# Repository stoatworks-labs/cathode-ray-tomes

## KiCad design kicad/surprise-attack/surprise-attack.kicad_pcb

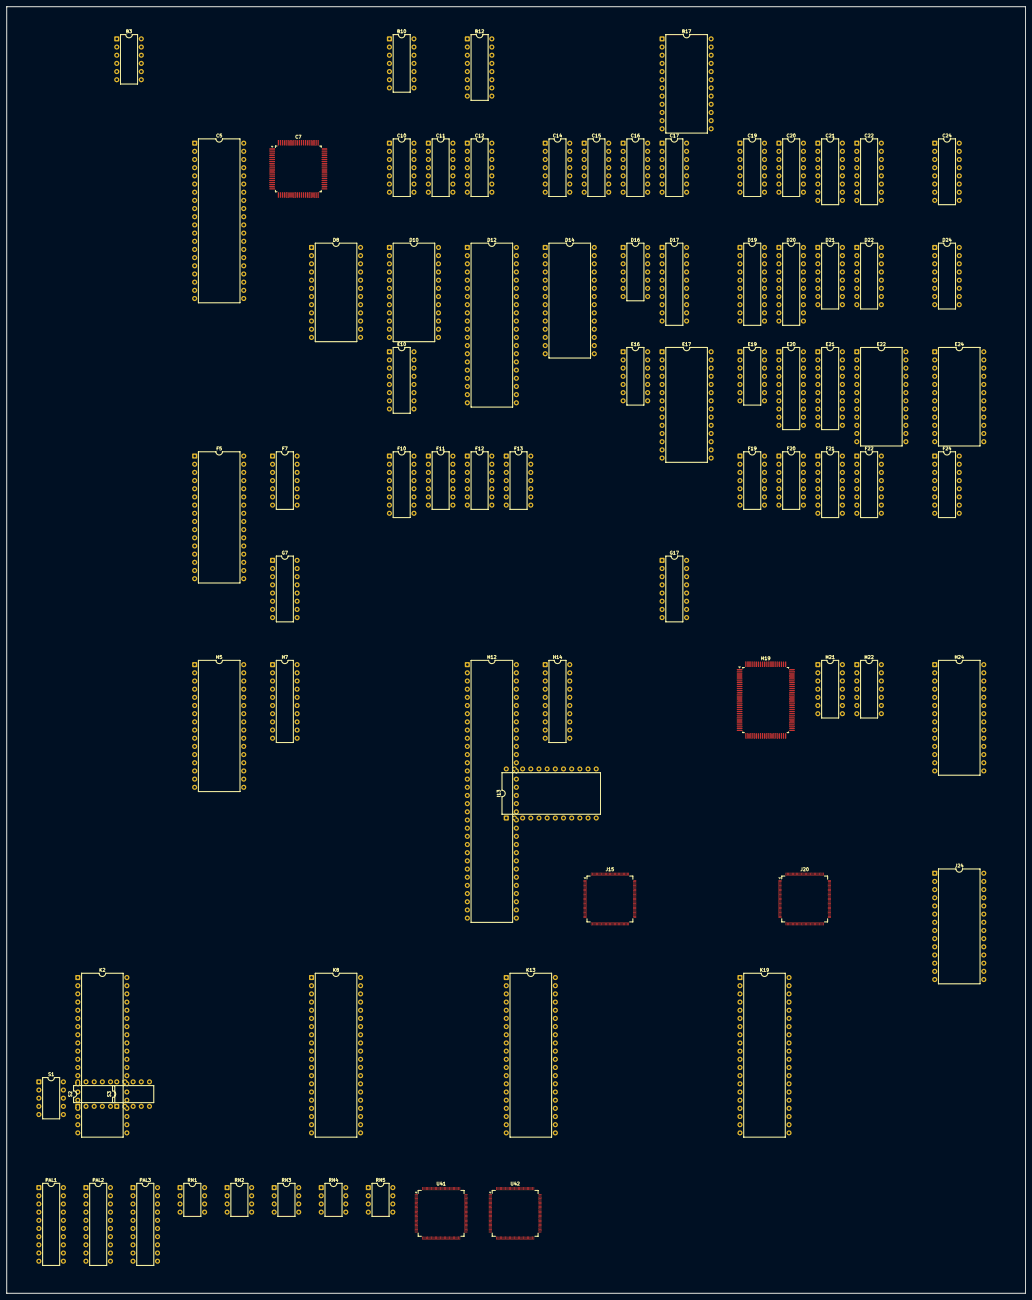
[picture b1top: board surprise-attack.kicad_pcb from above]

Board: 2 copper layers, 316.5 x 399.7 mm, 79 parts (0 on the bottom side), 536 nets, no tracks yet.

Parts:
B3: MB3722; DIP-12_W7.62mm
B10: LM324; DIP-14_W7.62mm
B12: YM3012; DIP-16_W7.62mm
B17: 051550; DIP-24_W15.24mm
C5: 955D04; DIP-40_W15.24mm
C7: 053260; PQFP-80_14x14mm_P0.65mm
C10: 74LS32; DIP-14_W7.62mm
C11: 74LS74; DIP-14_W7.62mm
C12: 74LS20; DIP-14_W7.62mm
C14: 74LS04; DIP-14_W7.62mm
C15, C16, C17, C19, C20: 74LS07; DIP-14_W7.62mm
C21, C22, C24: 74LS253; DIP-16_W7.62mm
D8: YM2151; DIP-24_W15.24mm
D10: CY7C128-45PC; DIP-24_W15.24mm
D12: Z80CPU; DIP-40_W15.24mm
D14: 27C512; DIP-28_W15.24mm
D16: 74LS74; DIP-14_W7.62mm
D17, D19, D20: 74LS273; DIP-20_W7.62mm
D21: 74LS253; DIP-16_W7.62mm
D22, D24: 74LS257; DIP-16_W7.62mm
E10: 74LS139; DIP-16_W7.62mm
E16: 74LS00; DIP-14_W7.62mm
E17: MB8464A-10W-15W; DIP-28_W15.24mm
E19: 74LS07; DIP-14_W7.62mm
E20, E21: 74LS245; DIP-20_W7.62mm
E22, E24: HM6116P-3; DIP-24_W15.24mm
F5: 27C010; DIP-32_W15.24mm
F7: 74LS04; DIP-14_W7.62mm
F10: 74LS367; DIP-16_W7.62mm
F11: 74LS08; DIP-14_W7.62mm
F12, F13: 74LS32; DIP-14_W7.62mm
F19: 74LS74; DIP-14_W7.62mm
F20: 74LS164; DIP-14_W7.62mm
F21, F22, F24: 74LS157; DIP-16_W7.62mm
G7: 74LS174; DIP-16_W7.62mm
G17: 74LS157; DIP-16_W7.62mm
H5: 27C010; DIP-32_W15.24mm
H7, H14: 74LS245; DIP-20_W7.62mm
H12: 053248; DIP-64_W15.24mm
H19: 053251; PQFP-100_14x20mm_P0.65mm
H21: 74LS04; DIP-14_W7.62mm
H22: 74LS74; DIP-14_W7.62mm
H24: MB8464A-10W-15W; DIP-28_W15.24mm
I13: HM6116P-3; DIP-24_W15.24mm
J15: 051962; TQFP-120_14x14mm_P0.4mm
J20: 052109; TQFP-120_14x14mm_P0.4mm
J24: MB8464A-10W-15W; DIP-28_W15.24mm
K2, K8, K13, K19: 955D05-06-07-08; DIP-40_W15.24mm
PAL1, PAL2, PAL3: PAL16L8; DIP-20_W7.62mm
RN1, RN2, RN3, RN4, RN5: KONAMI_005273; DIP-8_W7.62mm
S1, S2, S3: 052535; DIP-10_W7.62mm
U41: 053245; TQFP-120_14x14mm_P0.4mm
U42: 053244; TQFP-120_14x14mm_P0.4mm

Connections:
/+12V: B3.10, B17.19
/AUX1: C7.23, D8.21
/COIN_CNT_1: B17.22, B17.23
/COIN_CNT_2: B17.20, B17.21
/CPU~EN: D22.2, F13.9, U41.26
/DFI0: H19.47, J15.59
/DFI1: H19.48, J15.60
/DFI2: H19.49, J15.62
/DFI3: H19.50, J15.63
/DFI5: H19.51, J15.65
/DFI6: H19.52, J15.66
/DFI7: H19.54, J15.67
/DSA0: H19.66, J15.46
/DSA1: H19.67, J15.47
/DSA2: H19.68, J15.48
/DSA3: H19.69, J15.49
/DSA5: H19.70, J15.51
/DSA6: H19.71, J15.52
/DSA7: H19.72, J15.53
/DSB0: H19.57, J15.30
/DSB1: H19.58, J15.32
/DSB2: H19.59, J15.33
/DSB3: H19.60, J15.34
/DSB5: H19.61, J15.36
/DSB6: H19.62, J15.37
/DSB7: H19.63, J15.38
/FM~CS: D8.7, E10.4, PAL1.19
/GM12: J15.95, U41.12, U42.12
/IOCS: D22.15, D24.15, PAL1.13
/M6: D16.3, D19.11, D20.11, F20.8, H19.41, J15.78, U41.10, U42.10
/M12: F19.3, H21.11, H21.13, J20.103
/MAIN_A0: C7.18, D8.4, E17.10, F5.12, F7.5, F7.9, G17.11, H5.12, H12.14, H19.85, J15.88, J20.66, U41.9, U42.19
/MAIN_A1: E17.9, F5.11, F7.11, F24.2, H5.11, H12.13, H19.84, J15.89, J20.67, U41.25, U42.18
/MAIN_A2: E10.14, E17.8, F5.10, F24.5, H5.10, H12.12, H19.83, J20.68, U41.24, U42.17
/MAIN_A3: E10.13, E17.7, F5.9, F24.11, H5.9, H12.11, H19.82, J20.69, U41.23, U42.15
/MAIN_A4: E17.6, F5.8, F24.14, H5.8, H12.9, J20.116, PAL1.11, U41.22
/MAIN_A5: E17.5, F5.7, F22.2, H5.7, H12.8, J20.115, PAL1.9, U41.20
/MAIN_A6: E17.4, F5.6, F22.5, H5.6, H12.7, J20.114, PAL1.8, U41.19
/MAIN_A7: E17.3, F5.5, F22.11, H5.5, H12.6, J20.113, PAL1.5, U41.18
/MAIN_A8: E17.25, F5.27, F22.14, H5.27, H12.62, J20.112, PAL1.4, U41.17
/MAIN_A9: E17.24, F5.26, F21.2, H5.26, H12.61, J20.111, PAL1.3, U41.15
/MAIN_A10: E17.21, F5.23, F21.5, H5.23, H12.60, J20.110, PAL3.8, U41.14
/MAIN_A11: E17.23, F5.25, H5.25, H12.59, J20.109, PAL3.7
/MAIN_A12: E17.2, F5.4, H5.4, H12.56, J20.80, PAL3.6
/MAIN_A13: H12.55, J20.81, PAL2.5, PAL3.5
/MAIN_A14: H12.54, J20.82, PAL2.4, PAL3.4
/MAIN_A15: H12.53, J20.83, PAL2.3, PAL3.3
/MAIN_A16: H12.38, PAL2.9
/MAIN_A17: H12.39, PAL2.8
/MAIN_A18: H12.40, PAL2.7
/MAIN_A19: H12.41, PAL2.6
/MAIN_DB0: C7.8, C24.7, D8.10, D17.3, D22.4, E17.11, E20.2, E21.2, G7.3, H7.2, H14.2, H19.80, J15.79, J20.56, U42.29
/MAIN_DB1: C7.9, C24.9, D8.12, D17.4, D22.7, E17.12, E20.3, E21.3, G7.4, H7.3, H14.3, H19.79, J15.80, J20.57, U42.28
/MAIN_DB2: C7.10, C22.7, D8.13, D17.7, D22.9, E17.13, E20.4, E21.4, G7.6, H7.4, H14.4, H19.77, J15.81, J20.58, U42.27
/MAIN_DB3: C7.11, C22.9, D8.14, D17.8, D22.12, E17.15, E20.5, E21.5, H7.5, H14.5, H19.76, J15.82, J20.59, U42.26
/MAIN_DB4: C7.13, C21.7, D8.15, D17.13, D24.4, E17.16, E20.6, E21.6, H7.6, H14.6, H19.75, J15.83, J20.60, U42.25
/MAIN_DB5: C7.14, C21.9, D8.16, D17.14, D24.7, E17.17, E20.7, E21.7, G7.11, H7.7, H14.7, H19.74, J15.84, J20.62, U42.24
/MAIN_DB6: C7.15, D8.17, D17.17, D21.7, D24.9, E17.18, E20.8, E21.8, G7.13, H7.8, J15.85, J20.63, U42.23
/MAIN_DB7: C7.16, D8.18, D17.18, D21.9, D24.12, E17.19, E20.9, E21.9, G7.14, H7.9, H14.8, H14.9, J15.86, J20.64, U42.22
/MAIN~IRQ: H12.4, J20.87
/MBRIT0: D17.15, E16.5
/MBRIT1: D17.16, E16.13
/MBRIT2: D17.19, E16.2
/OBJPXL0: H19.30, U42.120
/OBJPXL1: H19.31, U42.119
/OBJPXL2: H19.32, U42.118
/OBJPXL3: H19.33, U42.117
/OBJPXL4: H19.34, U42.116
/OBJPXL5: H19.35, U42.115
/OBJPXL6: H19.36, U42.114
/OBJPXL7: H19.37, U42.113
/OBJPXL8: H19.38, U42.112
/PALETTE~CS: E20.1, E21.1, F11.5, F21.1, F21.14, F22.1, F24.1, G17.1, PAL3.14
/PAL_BANK: F21.11, G7.7
/PQ: F10.4, J20.89
/PR13: H19.25, U42.110
/PR14: H19.27, U42.109
/RMSCR~RD: D17.9, J15.96, J20.97, PAL1.2
/R/~W: C7.19, E17.27, F7.3, F12.2, F12.9, F12.13, H7.1, H12.15
/SCR_PE: F10.2, F19.11, J20.90
/SC~CS: C7.72, E10.6
/SDI0: H19.95, U42.108
/SH1: B12.6, C7.22, C11.11, D8.20
/SH2: B12.5, D8.19
/SND_A0: C7.70, D10.8, D12.30, D14.10
/SND_A1: C7.69, D10.7, D12.31, D14.9
/SND_A2: C7.68, D10.6, D12.32, D14.8
/SND_A3: C7.67, D10.5, D12.33, D14.7
/SND_A4: C7.66, D10.4, D12.34, D14.6
/SND_A5: C7.65, D10.3, D12.35, D14.5
/SND_A6: D10.2, D12.36, D14.4
/SND_A7: D10.1, D12.37, D14.3
/SND_A8: D10.23, D12.38, D14.25
/SND_A9: D10.22, D12.39, D14.24, E10.2
/SND_A10: D10.19, D12.40, D14.21, E10.3
/SND_A11: C10.10, C14.1, D12.1, D14.23
/SND_A12: C12.5, D12.2, D14.2
/SND_A13: C12.4, D12.3, D14.26
/SND_A14: C12.2, D12.4, D14.27
/SND_A15: C12.1, D12.5, D14.1
/SND_D0: C7.5, D10.9, D12.14, D14.11
/SND_D1: C7.4, D10.10, D12.15, D14.12
/SND_D2: C7.3, D10.11, D12.12, D14.13
/SND_D3: C7.2, D10.13, D12.8, D14.15
/SND_D4: C7.1, D10.14, D12.7, D14.16
/SND_D5: C7.80, D10.15, D12.9, D14.17
/SND_D6: C7.79, D10.16, D12.10, D14.18
/SND_D7: C7.78, D10.17, D12.13, D14.19
/SO~CLK: B12.2, D8.23
/S~CLK: C7.21, D12.6, F7.12
/S~RD: D10.20, D12.21, D14.22, F7.1
/WD_OUT1: B17.15, D17.2
/WD_OUT2: B17.16, D17.5
/colmix/BRIT: D16.2, H19.88
/colmix/BRITEN: D16.5, E16.1, E16.4, E16.12
/colmix/CO1: F24.3, H19.19
/colmix/CO2: F24.6, H19.18
/colmix/CO3: F24.10, H19.17
/colmix/CO4: F24.13, H19.16
/colmix/CO5: F22.3, H19.14
/colmix/CO6: F22.6, H19.13
/colmix/CO7: F22.10, H19.12
/colmix/CO8: F22.13, H19.11
/colmix/CO9: F21.3, H19.93
/colmix/CO10: F21.6, H19.92
/colmix/CO11: F21.10, H19.91
/colmix/MCO1: E22.19, E24.8, F24.4
/colmix/MCO2: E22.8, E24.7, F24.7
/colmix/MCO3: E22.5, E24.6, F24.9
/colmix/MCO4: E22.4, E24.5, F22.4
/colmix/MCO5: E22.6, E24.4, F22.12
/colmix/MCO6: E22.7, E24.3, F21.7
/colmix/MCO7: E22.23, E24.2, F21.9
/colmix/MCO8: E22.22, E24.1, F24.12
/colmix/MCO9: E22.1, E24.23, F22.9
/colmix/MCO10: E22.2, E24.22, F21.4
/colmix/MCO11: E22.3, E24.19, F22.7
/colmix/MCO~OE: E22.20, E24.20, F21.12
/colmix/MCO~WRH: E24.21, F13.6
/colmix/MCO~WRL: E22.21, F13.3
/colmix/RGB0: D19.3, E21.18, E22.9
/colmix/RGB1: D19.4, E21.17, E22.10
/colmix/RGB2: D19.7, E21.16, E22.11
/colmix/RGB3: D19.8, E21.15, E22.13
/colmix/RGB4: D19.13, E21.14, E22.14
/colmix/RGB5: D19.14, E21.13, E22.15
/colmix/RGB6: D19.17, E21.12, E22.16
/colmix/RGB7: E21.11, E22.17
/colmix/RGB8: D20.3, E20.18, E24.9
/colmix/RGB9: D20.4, E20.17, E24.10
/colmix/RGB10: D20.7, E20.16, E24.11
/colmix/RGB11: D20.8, E20.15, E24.13
/colmix/RGB12: D20.13, E20.14, E24.14
/colmix/RGB13: D20.14, E20.13, E24.15
/colmix/RGB14: D20.17, E20.12, E24.16
/colmix/RGB15: D20.18, E20.11, E24.17
/colmix/SDO1: C14.5, H19.87
/colmix/rgb/B0: C17.5, D19.6
/colmix/rgb/B1: C16.11, D19.9
/colmix/rgb/B2: C16.9, D19.12
/colmix/rgb/B3: C15.9, D19.15
/colmix/rgb/B4: C15.11, D19.16
/colmix/rgb/G0: C17.9, D20.15
/colmix/rgb/G1: C19.3, D20.16
/colmix/rgb/G2: C20.13, D20.19
/colmix/rgb/G3: C19.5, D19.2
/colmix/rgb/G4: C17.3, D19.5
/colmix/rgb/R0: C20.9, D20.2
/colmix/rgb/R1: C20.1, D20.5
/colmix/rgb/R2: C20.5, D20.6
/colmix/rgb/R3: C20.3, D20.9
/colmix/rgb/R4: C20.11, D20.12
/colmix/rgb/~MBRIT0: E16.6, E19.1, E19.11, E19.13
/colmix/rgb/~MBRIT1: C19.1, C19.11, C19.13, E16.11
/colmix/rgb/~MBRIT2: C17.1, C17.11, C17.13, E16.3
/colmix/rgb/~SHADOW: C16.1, C16.3, C16.13, D19.19
/colmix/~COCEH: E20.19, F13.4, G17.12
/colmix/~COCEL: E21.19, F13.1, G17.9
/colmix/~CS: F12.11, H19.81
/io_cabinet/I1P_BTN_1: C21.13, RN5.5
/io_cabinet/I1P_BTN_2: D21.3, RN1.1
/io_cabinet/I1P_BTN_3: D21.13, RN1.5
/io_cabinet/I1P_DOWN: C22.3, RN3.1
/io_cabinet/I1P_LEFT: C22.13, RN3.5
/io_cabinet/I1P_RIGHT: C21.3, RN5.1
/io_cabinet/I1P_START: C24.3, RN2.1
/io_cabinet/I1P_UP: C24.13, RN2.5
/io_cabinet/I2P_BTN_1: C21.12, RN5.7
/io_cabinet/I2P_BTN_2: D21.4, RN1.3
/io_cabinet/I2P_BTN_3: D21.12, RN1.7
/io_cabinet/I2P_DOWN: C22.4, RN3.3
/io_cabinet/I2P_LEFT: C22.12, RN3.7
/io_cabinet/I2P_RIGHT: C21.4, RN5.3
/io_cabinet/I2P_START: C24.4, RN2.3
/io_cabinet/I2P_UP: C24.12, RN2.7
/io_cabinet/ICOIN_1: C22.5, RN4.5
/io_cabinet/ICOIN_2: C22.11, RN4.7
/io_cabinet/ISERVICE1: C24.5, RN4.1
/io_cabinet/ISERVICE2: C24.11, RN4.3
/io_cabinet/~A0: C21.14, C22.14, C24.14, D21.14, D22.1, D24.1, F7.6
/io_cabinet/~A1: C21.2, C22.2, C24.2, D21.2, F7.10
/main/AS: F19.4, F19.10, H21.4, H22.1, PAL1.1
/main/BANK1: G7.5, PAL3.9
/main/BANKR: D17.12, PAL3.2
/main/BANK~CS: E10.11, G7.9
/main/DTAC: F11.6, H12.49
/main/MAIN_A20: H12.43, PAL2.18
/main/MAIN_D0: F5.13, H5.13, H7.18, H12.21
/main/MAIN_D1: F5.14, H5.14, H7.17, H12.22
/main/MAIN_D2: F5.15, H5.15, H7.16, H12.23
/main/MAIN_D3: F5.17, H5.17, H7.15, H12.24
/main/MAIN_D4: F5.18, H5.18, H7.14, H12.27
/main/MAIN_D5: F5.19, H5.19, H7.13, H12.28
/main/MAIN_D6: F5.20, H5.20, H7.12, H12.29
/main/MAIN_D7: F5.21, H5.21, H7.11, H12.30
/main/MAIN~CLK: H12.18, H21.12
/main/MAIN~RST: F10.7, H12.2
/main/MISC: E10.15, PAL1.14
/main/MPQ: F10.5, H12.17
/main/NC: PAL2.1, PAL3.18
/main/PE: F10.3, H12.51
/main/PROG_A13: F5.28, H5.28, PAL2.12
/main/PROG_A14: F5.29, H5.29, PAL2.13
/main/PROG_A15: F5.3, H5.3, PAL2.14
/main/PROG_A16: F5.2, H5.2, PAL2.15
/main/WORK~CS: E17.20, PAL3.16
/main/~AS: F19.12, H12.16, H21.3, PAL3.1
/main/~M12: H21.10, H22.3
/main/~PAGED: E16.10, PAL2.11, PAL3.17
/main/~PROGCS1: F5.24, PAL2.17
/main/~PROGCS2: E16.9, H5.24, PAL2.16
/main/~UNPAGED: PAL2.2, PAL3.19
/main/~WRK: G7.2, PAL3.11
/main/~i6: PAL1.6, PAL3.13
/main/~i7: PAL1.7, PAL3.12
/objects/AR0: U41.119, U42.30
/objects/AR1: U41.118, U42.32
/objects/AR2: U41.117, U42.33
/objects/AROK: U41.116, U42.34
/objects/BR0: U41.115, U42.35
/objects/BR1: U41.114, U42.36
/objects/BR2: U41.113, U42.37
/objects/BROK: U41.112, U42.38
/objects/CLAT: U41.86, U42.64
/objects/HP0: U41.96, U42.54
/objects/HP1: U41.97, U42.53
/objects/HP2: U41.98, U42.52
/objects/HP3: U41.99, U42.50
/objects/HP4: U41.100, U42.49
/objects/HP5: U41.102, U42.48
/objects/HP6: U41.103, U42.47
/objects/HP7: U41.104, U42.45
/objects/HP8: U41.105, U42.44
/objects/HP9: U41.107, U42.43
/objects/HRFP: U41.110, U42.39
/objects/OBJRAMD0: H14.18, I13.9, U41.45
/objects/OBJRAMD1: H14.17, I13.10, U41.44
/objects/OBJRAMD2: H14.16, I13.11, U41.43
/objects/OBJRAMD3: H14.15, I13.13, U41.42
/objects/OBJRAMD4: H14.14, I13.14, U41.40
/objects/OBJRAMD5: H14.13, I13.15, U41.39
/objects/OBJRAMD6: H14.12, I13.16, U41.38
/objects/OBJRAMD7: H14.11, I13.17, U41.37
/objects/OBJROMA0: K2.9, K8.9, U41.85
/objects/OBJROMA1: K2.8, K8.8, U41.84
/objects/OBJROMA2: K2.7, K8.7, U41.83
/objects/OBJROMA3: K2.6, K8.6, U41.82
/objects/OBJROMA4: K2.5, K8.5, U41.80
/objects/OBJROMA5: K2.4, K8.4, U41.79
/objects/OBJROMA6: K2.3, K8.3, U41.78
/objects/OBJROMA7: K2.2, K8.2, U41.77
/objects/OBJROMA8: K2.40, K8.40, U41.75
/objects/OBJROMA9: K2.39, K8.39, U41.74
/objects/OBJROMA10: K2.38, K8.38, U41.73
/objects/OBJROMA11: K2.37, K8.37, U41.72
/objects/OBJROMA12: K2.36, K8.36, U41.70
/objects/OBJROMA13: K2.35, K8.35, U41.69
/objects/OBJROMA14: K2.34, K8.34, U41.68
/objects/OBJROMA15: K2.33, K8.33, U41.67
/objects/OBJROMA16: K2.32, K8.32, U41.66
/objects/OBJROMA17: K2.1, K8.1, U41.65
/objects/OBJROMD0: K2.13, U42.83
/objects/OBJROMD1: K2.15, U42.82
/objects/OBJROMD2: K2.17, U42.80
/objects/OBJROMD3: K2.19, U42.79
/objects/OBJROMD4: K2.22, U42.78
/objects/OBJROMD5: K2.24, U42.77
/objects/OBJROMD6: K2.26, U42.75
/objects/OBJROMD7: K2.28, U42.74
/objects/OBJROMD8: K2.14, U42.73
/objects/OBJROMD9: K2.16, U42.72
/objects/OBJROMD10: K2.18, U42.70
/objects/OBJROMD11: K2.20, U42.69
/objects/OBJROMD12: K2.23, U42.68
/objects/OBJROMD13: K2.25, U42.67
/objects/OBJROMD14: K2.27, U42.66
/objects/OBJROMD15: K2.29, U42.65
/objects/OBJROMD16: K8.13, U42.100
/objects/OBJROMD17: K8.15, U42.99
/objects/OBJROMD18: K8.17, U42.98
/objects/OBJROMD19: K8.19, U42.97
/objects/OBJROMD20: K8.22, U42.96
/objects/OBJROMD21: K8.24, U42.95
/objects/OBJROMD22: K8.26, U42.94
/objects/OBJROMD23: K8.28, U42.93
/objects/OBJROMD24: K8.14, U42.92
/objects/OBJROMD25: K8.16, U42.90
/objects/OBJROMD26: K8.18, U42.89
/objects/OBJROMD27: K8.20, U42.88
/objects/OBJROMD28: K8.23, U42.87
/objects/OBJROMD29: K8.25, U42.86
/objects/OBJROMD30: K8.27, U42.85
/objects/OBJROMD31: K8.29, U42.84
/objects/ORAMA0: I13.3, U41.50
/objects/ORAMA1: I13.4, U41.52
/objects/ORAMA2: I13.5, U41.53
/objects/ORAMA3: I13.23, U41.54
/objects/ORAMA4: I13.6, U41.55
/objects/ORAMA5: I13.22, U41.56
/objects/ORAMA6: I13.7, U41.57
/objects/ORAMA7: I13.8, U41.58
/objects/ORAMA8: I13.19, U41.59
/objects/ORAMA9: I13.2, U41.62
/objects/ORAMA10: I13.1, U41.63
/objects/PL0: U41.87, U42.63
/objects/PL1: U41.88, U42.62
/objects/PL2: U41.89, U42.60
/objects/PL3: U41.90, U42.59
/objects/PL4: U41.92, U42.58
/objects/PL5: U41.93, U42.57
/objects/PL6: U41.94, U42.56
/objects/SHADOW: U41.95, U42.55
/objects/~HIT: U41.108, U42.42
/objects/~OBJRAM_RD: F13.11, H14.1
/objects/~ZLD: U41.109, U42.40
/pcm/RA0: C5.29, C7.39
/pcm/RA1: C5.9, C7.40
/pcm/RA2: C5.8, C7.41
/pcm/RA3: C5.7, C7.42
/pcm/RA4: C5.6, C7.44
/pcm/RA5: C5.5, C7.45
/pcm/RA6: C5.4, C7.46
/pcm/RA7: C5.3, C7.47
/pcm/RA8: C5.2, C7.48
/pcm/RA9: C5.40, C7.49
/pcm/RA10: C5.39, C7.50
/pcm/RA11: C5.38, C7.51
/pcm/RA12: C5.37, C7.53
/pcm/RA13: C5.36, C7.54
/pcm/RA14: C5.35, C7.55
/pcm/RA15: C5.34, C7.56
/pcm/RA16: C5.33, C7.57
/pcm/RA17: C5.32, C7.58
/pcm/RA18: C5.1, C7.59
/pcm/RD0: C5.13, C7.29
/pcm/RD1: C5.15, C7.30
/pcm/RD2: C5.17, C7.31
/pcm/RD3: C5.19, C7.32
/pcm/RD4: C5.22, C7.35
/pcm/RD5: C5.24, C7.36
/pcm/RD6: C5.26, C7.37
/pcm/RD7: C5.28, C7.38
/scroll/COL5: J15.109, J20.42
/scroll/COL6: J15.108, J20.43
/scroll/GFXROMA0: J20.35, K13.9, K19.9
/scroll/GFXROMA1: J20.34, K13.8, K19.8
/scroll/GFXROMA2: J20.33, K13.7, K19.7
/scroll/GFXROMA3: J20.32, K13.6, K19.6
/scroll/GFXROMA4: J20.30, K13.5, K19.5
/scroll/GFXROMA5: J20.29, K13.4, K19.4
/scroll/GFXROMA6: J20.28, K13.3, K19.3
/scroll/GFXROMA7: J20.27, K13.2, K19.2
/scroll/GFXROMA8: J20.26, K13.40, K19.40
/scroll/GFXROMA9: J20.25, K13.39, K19.39
/scroll/GFXROMA10: J20.24, K13.38, K19.38
/scroll/GFXROMA11: J20.37, K13.37, K19.37
/scroll/GFXROMA12: J20.38, K13.36, K19.36
/scroll/GFXROMA13: J20.41, K13.35, K19.35
/scroll/GFXROMA14: J20.39, K13.34, K19.34
/scroll/GFXROMA15: J20.40, K13.33, K19.33
/scroll/GFXROMA16: J20.23, K13.32, K19.32
/scroll/GFXROMA17: J20.22, K13.1, K19.1
/scroll/GFXROMD0: J15.29, K13.13
/scroll/GFXROMD1: J15.28, K13.15
/scroll/GFXROMD2: J15.27, K13.17
/scroll/GFXROMD3: J15.26, K13.19
/scroll/GFXROMD4: J15.25, K13.22
/scroll/GFXROMD5: J15.24, K13.24
/scroll/GFXROMD6: J15.23, K13.26
/scroll/GFXROMD7: J15.22, K13.28
/scroll/GFXROMD8: J15.21, K13.14
/scroll/GFXROMD9: J15.20, K13.16
/scroll/GFXROMD10: J15.19, K13.18
/scroll/GFXROMD11: J15.18, K13.20
/scroll/GFXROMD12: J15.17, K13.23
/scroll/GFXROMD13: J15.16, K13.25
/scroll/GFXROMD14: J15.13, K13.27
/scroll/GFXROMD15: J15.12, K13.29
/scroll/GFXROMD16: J15.11, K19.13
/scroll/GFXROMD17: J15.10, K19.15
/scroll/GFXROMD18: J15.9, K19.17
/scroll/GFXROMD19: J15.8, K19.19
/scroll/GFXROMD20: J15.7, K19.22
/scroll/GFXROMD21: J15.6, K19.24
/scroll/GFXROMD22: J15.5, K19.26
/scroll/GFXROMD23: J15.4, K19.28
/scroll/GFXROMD24: J15.3, K19.14
/scroll/GFXROMD25: J15.2, K19.16
/scroll/GFXROMD26: J15.120, K19.18
/scroll/GFXROMD27: J15.119, K19.20
/scroll/GFXROMD28: J15.118, K19.23
/scroll/GFXROMD29: J15.117, K19.25
/scroll/GFXROMD30: J15.116, K19.27
/scroll/GFXROMD31: J15.115, K19.29
/scroll/M24: H21.6, J15.90, J20.65
/scroll/SCRAMA0: H24.10, J20.2, J24.10
/scroll/SCRAMA1: H24.9, J20.120, J24.9
/scroll/SCRAMA2: H24.8, J20.119, J24.8
/scroll/SCRAMA3: H24.7, J20.118, J24.7
/scroll/SCRAMA4: H24.6, J20.117, J24.6
/scroll/SCRAMA5: H24.5, J20.70, J24.5
/scroll/SCRAMA6: H24.4, J20.71, J24.4
/scroll/SCRAMA7: H24.3, J20.72, J24.3
/scroll/SCRAMA8: H24.25, J20.73, J24.25
/scroll/SCRAMA9: H24.24, J20.76, J24.24
/scroll/SCRAMA10: H24.21, J20.77, J24.21
/scroll/SCRAMA11: H24.23, J20.78, J24.23
/scroll/SCRAMA12: H24.2, J20.79, J24.2
/scroll/VD0: H24.11, J20.20
/scroll/VD1: H24.12, J20.19
/scroll/VD2: H24.13, J20.18
/scroll/VD3: H24.15, J20.17
/scroll/VD4: H24.16, J20.16
/scroll/VD5: H24.17, J20.13
/scroll/VD6: H24.18, J20.12
/scroll/VD7: H24.19, J20.11
/scroll/VD8: J20.10, J24.11
/scroll/VD9: J20.9, J24.12
/scroll/VD10: J20.8, J24.13
/scroll/VD11: J20.7, J24.15
/scroll/VD12: J20.6, J24.16
/scroll/VD13: J20.5, J24.17
/scroll/VD14: J20.4, J24.18
/scroll/VD15: J20.3, J24.19
/scroll/ZA1H: J15.101, J20.50
/scroll/ZA2H: J15.100, J20.51
/scroll/ZA4H: J15.99, J20.52
/scroll/ZB1H: J15.106, J20.47
/scroll/ZB2H: J15.103, J20.48
/scroll/ZB4H: J15.102, J20.49
/scroll/~BE: J15.98, J20.53
/scroll/~RCS1: J20.93, J24.20
/scroll/~ROE1: J20.95, J24.22
/scroll/~ROE2: H24.22, J20.96
/scroll/~RWE1: J20.107, J24.27
/scroll/~RWE2: H24.27, J20.108
/sound/SND~E: C10.11, E10.1
/sound/SRAM~CE: C10.8, D10.18
/sound/SROM~CE: C14.8, D14.20
/sound/S~IORQ: D12.20, F11.2
/sound/S~MREQ: C10.5, D12.19
/sound/S~WR: D10.21, D12.22
/sound/~RFSH: C14.13, D12.28
/sound/~SET: C11.10, E10.5
/~HBLANK: F20.2, J15.70
/~HSYNC: J15.73, U41.4, U42.8
/~JOYSTK: C21.1, C21.15, C22.1, C22.15, C24.1, C24.15, D21.1, D21.15, PAL1.12
/~MDS: D8.5, F13.2, F13.5, H12.20, U42.14
/~OBJRAM_CS: F11.12, F12.10, PAL3.15
/~OBJSET: C14.11, F11.13, PAL1.17, U41.6, U42.13
/~OUTCS: E10.12, F12.1, F12.4
/~PCU_CS: F12.12, PAL1.16
/~RCS0: J20.92, U41.3, U42.3
/~RD: D8.6, E17.22, F7.4, F12.5, F13.12, J15.87, J20.85, U41.13, U42.20
/~RESET: D17.1, F10.6, G7.1, J20.98
/~SOON: D16.11, E10.10
/~VBLANK: F20.1, J15.69
/~VCS: H22.2, J15.97, J20.54, J20.84, PAL1.18
/~VSYNC: J15.72, U41.5, U42.9
/~WDOGRST: B12.7, C7.75, C11.13, D8.3, D12.26, F11.1, F20.9, H22.9, J15.92, J20.55
/~WDRST: B17.10, H22.12, H22.13
GND: B3.6, B3.7, B10.11, B12.3, B12.8, B12.16, B17.13, B17.14, C5.10, C5.11, C5.12, C5.30, C5.31, C7.12, C7.34, C7.43, C7.52, C7.61, C7.74, C10.7, C11.7, C11.12, C12.7, C14.7, C15.7, C16.7, C17.7, C19.7, C20.7, C21.8, C22.8, C24.8, D8.1, D8.11, D10.12, D12.29, D14.14, D16.7, D17.10, D19.10, D20.10, D21.8, D22.3, D22.8, D24.6, D24.8, E10.8, E16.7, E17.14, E19.7, E22.12, E22.18, E24.12, E24.18, F5.16, F5.22, F7.7, F10.1, F10.8, F11.7, F12.7, F13.7, F19.7, F20.7, F21.13, F21.15, F22.15, F24.15, G7.8, G17.15, H5.16, H5.22, H12.1, H12.5, H12.10, H12.19, H12.25, H12.31, H12.32, H12.33, H12.34, H12.35, H12.36, H12.37, H12.42, H12.47, H12.48, H12.52, H12.57, H19.4, H19.5, H19.6, H19.7, H19.8, H19.9, H19.10, H19.15, H19.20, H19.21, H19.22, H19.23, H19.24, H19.40, H19.55, H19.56, H19.64, H19.65, H19.73, H19.90, H19.94, H19.96, H21.7, H22.7, H24.14, H24.20, I13.12, I13.18, J15.1, J15.15, J15.31, J15.45, J15.61, J15.75, J15.91, J15.94, J15.105, J15.107, J15.110, J15.111, J15.112, J15.113, J20.1, J20.15, J20.21, J20.31, J20.45, J20.61, J20.75, J20.91, J20.105, J24.14, K2.10, K2.11, K2.12, K2.30, K8.10, K8.11, K8.12, K8.30, K13.10, K13.11, K13.12, K13.30, K19.10, K19.11, K19.12, K19.30, PAL1.10, PAL2.10, PAL3.10, S1.9, S2.9, S3.9, U41.1, U41.2, U41.8, U41.11, U41.21, U41.31, U41.41, U41.51, U41.61, U41.71, U41.81, U41.91, U41.101, U41.111, U42.1, U42.2, U42.11, U42.21, U42.31, U42.41, U42.51, U42.61, U42.71, U42.81, U42.91, U42.101, U42.111
unnamed: B10.3, B12.15
unnamed: B10.2, B12.14
unnamed: B10.5, B12.9
unnamed: B10.6, B10.7
unnamed: B10.10, B12.12
unnamed: B10.8, B10.9
unnamed: B10.12, B12.10
unnamed: B10.13, B10.14
unnamed: B10.1, B12.13
unnamed: B17.1, F12.6
unnamed: C7.71, F7.2
unnamed: C10.1, C14.12
unnamed: C10.2, C12.6, C14.9
unnamed: C10.3, C10.4
unnamed: C11.9, D12.17
unnamed: C14.10, F13.13
unnamed: D12.16, D16.8
unnamed: D16.13, F11.3
unnamed: D17.11, F12.3
unnamed: C14.6, D19.18
unnamed: F11.11, F13.10
unnamed: F11.8, F19.2
unnamed: F11.4, F19.5
unnamed: F11.9, F19.9
unnamed: C15.1, C15.3, C15.13, F20.11
unnamed: F7.8, G17.14
unnamed: H21.1, H21.5
unnamed: E16.8, H7.19
unnamed: F13.8, H14.19
unnamed: F11.10, H22.6
unnamed: H21.2, H22.11
unnamed: I13.20, U41.49
unnamed: I13.21, U41.47
unnamed: C15.5, J15.76
unnamed: C15.2, S1.7
unnamed: C17.6, S1.6
unnamed: C16.10, S1.5
unnamed: C16.8, S1.4
unnamed: C15.8, S1.3
unnamed: C15.10, S1.2
unnamed: C15.12, S2.7
unnamed: C17.8, S2.6
unnamed: C19.4, S2.5
unnamed: C20.12, S2.4
unnamed: C19.6, S2.3
unnamed: C17.4, S2.2
unnamed: C15.4, S3.7
unnamed: C20.8, S3.6
unnamed: C20.2, S3.5
unnamed: C20.6, S3.4
unnamed: C20.4, S3.3
unnamed: C20.10, S3.2
unnamed: F12.8, U41.7
VCC: B10.4, B12.1, B17.9, C5.21, C7.20, C7.33, C7.73, C10.14, C11.14, C12.14, C14.14, C15.14, C16.14, C17.14, C19.14, C20.14, C21.16, C22.16, C24.16, D8.22, D10.24, D12.11, D14.28, D16.1, D16.4, D16.10, D16.12, D16.14, D17.20, D19.1, D19.20, D20.1, D20.20, D21.16, D22.16, D24.2, D24.5, D24.11, D24.14, D24.16, E10.16, E16.14, E17.26, E17.28, E19.14, E22.24, E24.24, F5.1, F5.31, F5.32, F7.14, F10.16, F11.14, F12.14, F13.14, F19.1, F19.13, F19.14, F20.14, G7.16, G17.10, G17.13, H5.1, H5.31, H5.32, H12.26, H12.50, H12.58, H19.1, H19.2, H19.3, H19.28, H19.29, H19.39, H19.42, H19.43, H19.44, H19.45, H19.46, H19.53, H19.78, H19.97, H19.98, H19.99, H19.100, H21.14, H22.4, H22.10, H22.14, H24.26, H24.28, I13.24, J15.14, J15.44, J15.74, J15.104, J20.14, J20.44, J20.74, J20.104, J24.26, J24.28, K2.21, K2.31, K8.21, K8.31, K13.21, K13.31, K19.21, K19.31, PAL1.20, PAL2.20, PAL3.20, S1.1, S2.1, S3.1, U41.16, U41.46, U41.60, U41.76, U41.106, U41.120, U42.16, U42.46, U42.76, U42.106

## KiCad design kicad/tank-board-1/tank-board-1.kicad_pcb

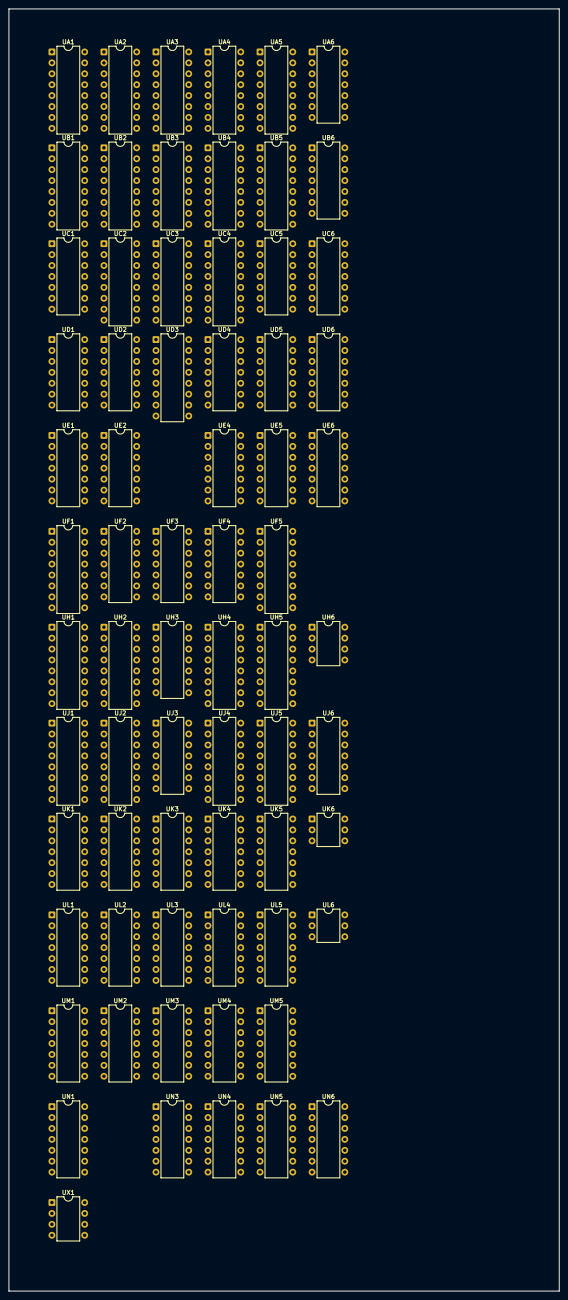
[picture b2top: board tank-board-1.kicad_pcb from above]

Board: 2 copper layers, 128.0 x 298.2 mm, 69 parts (0 on the bottom side), 179 nets, no tracks yet.

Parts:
UA1, UA2, UA4, UA5: 9316; DIP-16_W7.62mm
UA3: 74165; DIP-16_W7.62mm
UA6: 74H04; DIP-14_W7.62mm
UB1, UB2, UB4, UB5: 9316; DIP-16_W7.62mm
UB3: 74165; DIP-16_W7.62mm
UB6: 7404; DIP-14_W7.62mm
UC1, UC5: 7400; DIP-14_W7.62mm
UC2, UC4: 9316; DIP-16_W7.62mm
UC3: 74165; DIP-16_W7.62mm
UC6: 7402; DIP-14_W7.62mm
UD1, UD2, UD4, UD5: 7474; DIP-14_W7.62mm
UD3: 74165; DIP-16_W7.62mm
UD6: 7402; DIP-14_W7.62mm
UE1, UE2, UE4, UE5: 7474; DIP-14_W7.62mm
UE6: 74107; DIP-14_W7.62mm
UF1, UF5: 9316; DIP-16_W7.62mm
UF2, UF4: 7408; DIP-14_W7.62mm
UF3: 7474; DIP-14_W7.62mm
UH1, UH2, UH4, UH5: 9316; DIP-16_W7.62mm
UH3: 7404; DIP-14_W7.62mm
UH6: NE555; DIP-8_W7.62mm
UJ1, UJ2, UJ4, UJ5: 9316; DIP-16_W7.62mm
UJ3: 7404; DIP-14_W7.62mm
UJ6: 7474; DIP-14_W7.62mm
UK1, UK5: 7402; DIP-14_W7.62mm
UK2, UK3, UK4: 7486; DIP-14_W7.62mm
UK6: MFC6040; DIP-6_W7.62mm
UL1, UL5: 74107; DIP-14_W7.62mm
UL2, UL4: 7420; DIP-14_W7.62mm
UL3: 7402; DIP-14_W7.62mm
UL6: MFC6040; DIP-6_W7.62mm
UM1, UM5: 74S20; DIP-14_W7.62mm
UM2, UM4: 7410; DIP-14_W7.62mm
UM3: 74H08; DIP-14_W7.62mm
UN1, UN5: 74107; DIP-14_W7.62mm
UN3: 7474; DIP-14_W7.62mm
UN4: 7404; DIP-14_W7.62mm
UN6: 7402; DIP-14_W7.62mm
UX1: UA741; DIP-8_W7.62mm

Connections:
+5V: UA1.7, UA1.10, UA1.16, UA2.7, UA2.10, UA2.16, UA3.10, UA3.16, UA4.7, UA4.10, UA4.16, UA5.7, UA5.10, UA5.16, UA6.14, UB1.3, UB1.4, UB1.5, UB1.10, UB1.16, UB2.3, UB2.4, UB2.5, UB2.6, UB2.10, UB2.16, UB3.16, UB4.3, UB4.4, UB4.5, UB4.6, UB4.10, UB4.16, UB5.3, UB5.4, UB5.5, UB5.10, UB5.16, UB6.14, UC1.14, UC2.3, UC2.5, UC2.6, UC2.16, UC3.10, UC3.16, UC4.3, UC4.5, UC4.6, UC4.16, UC5.14, UC6.14, UD1.1, UD1.13, UD1.14, UD2.4, UD2.10, UD2.14, UD3.16, UD4.4, UD4.10, UD4.14, UD5.1, UD5.13, UD5.14, UD6.14, UE1.1, UE1.10, UE1.14, UE2.4, UE2.10, UE2.14, UE4.4, UE4.10, UE4.14, UE5.1, UE5.10, UE5.14, UE6.1, UE6.4, UE6.14, UF1.1, UF1.7, UF1.10, UF1.16, UF2.14, UF3.1, UF3.13, UF3.14, UF4.14, UF5.1, UF5.7, UF5.10, UF5.16, UH1.1, UH1.3, UH1.4, UH1.5, UH1.6, UH1.10, UH1.16, UH2.1, UH2.7, UH2.10, UH2.16, UH3.14, UH4.1, UH4.7, UH4.10, UH4.16, UH5.1, UH5.3, UH5.4, UH5.5, UH5.6, UH5.10, UH5.16, UH6.8, UJ1.1, UJ1.3, UJ1.5, UJ1.6, UJ1.16, UJ2.1, UJ2.3, UJ2.4, UJ2.5, UJ2.10, UJ2.16, UJ3.14, UJ4.1, UJ4.3, UJ4.4, UJ4.5, UJ4.10, UJ4.16, UJ5.1, UJ5.3, UJ5.5, UJ5.6, UJ5.16, UJ6.4, UJ6.10, UJ6.14, UK1.14, UK2.14, UK3.14, UK4.14, UK5.14, UL1.1, UL1.4, UL1.8, UL1.11, UL1.14, UL2.14, UL3.14, UL4.14, UL5.1, UL5.4, UL5.8, UL5.11, UL5.14, UM1.14, UM2.14, UM3.14, UM4.14, UM5.14, UN1.1, UN1.4, UN1.8, UN1.11, UN1.14, UN3.1, UN3.13, UN3.14, UN4.14, UN5.1, UN5.4, UN5.8, UN5.11, UN5.14, UN6.14
+12V: UK6.4, UL6.4, UX1.7
ATTRACT: UD6.6, UE6.6
ATTRACTQ: UD6.12, UE6.5, UH6.4, UN6.9
CLOCK1: UA1.2, UA3.2, UA6.8, UB1.2, UB3.2, UF3.11, UH2.2, UJ2.2
CLOCKQ: UA6.5, UA6.9, UH4.2, UJ4.2
COIN: UE6.12, UJ6.5
COIN1_NC: UB6.10, UB6.13, UD6.9
COIN1_NO: UB6.11, UB6.12, UN6.5
COIN2_NC: UB6.1, UB6.6, UD6.8
COIN2_NO: UB6.2, UB6.5, UN6.6
COINQ: UD6.2, UJ6.6
EXPL1: UJ3.13, UL2.10
EXPL2: UH3.11, UL4.9
FIRE1Q: UC1.4, UJ3.5, UM2.1, UM2.2
FIRE2Q: UC5.1, UH3.9, UM4.1, UM4.2
FLASH: UC1.10, UC5.12, UJ3.3
FLASHQ: UJ3.4, UK3.4, UK3.12
FPE1: UC1.6, UK1.9, UL3.2
FPE2: UC5.3, UC6.6, UC6.8
GND: UA1.8, UA2.8, UA3.8, UA4.8, UA5.8, UA6.7, UB1.6, UB1.8, UB2.8, UB3.8, UB4.8, UB5.6, UB5.8, UB6.7, UC1.7, UC2.4, UC2.8, UC3.8, UC4.4, UC4.8, UC5.7, UC6.7, UD1.7, UD2.7, UD3.8, UD4.7, UD5.7, UD6.7, UE1.7, UE2.7, UE4.7, UE5.7, UE6.7, UF1.8, UF2.7, UF3.7, UF4.7, UF5.8, UH1.8, UH2.8, UH3.7, UH4.8, UH5.8, UH6.1, UJ1.4, UJ1.8, UJ2.6, UJ2.8, UJ3.7, UJ4.6, UJ4.8, UJ5.4, UJ5.8, UJ6.7, UK1.7, UK2.7, UK3.7, UK4.7, UK5.7, UK6.1, UL1.7, UL2.7, UL3.7, UL4.7, UL5.7, UL6.1, UM1.7, UM2.7, UM3.7, UM4.7, UM5.7, UN1.7, UN3.2, UN3.7, UN3.12, UN4.7, UN5.7, UN6.7
HCOUNT2: UA4.2, UA6.4, UB4.2, UC4.2, UF5.2, UH5.2, UJ5.2
HMCE_B1: UC1.2, UC5.4, UF2.4, UF2.10, UF2.13, UF4.1, UF4.4, UF4.10, UJ3.8
HRST1Q: UA1.1, UB1.1, UN1.10, UN1.13
HRST2Q: UA5.1, UB5.1, UN5.10, UN5.13
H_COUNT1: UA2.2, UA6.2, UB2.2, UC2.2, UF1.2, UH1.2, UJ1.2
H_COUNTQ: UA6.1, UA6.3
unnamed: UH6.6, UH6.7
unnamed: UE6.10, UN4.4
unnamed: UA1.15, UB1.7, UM1.5
unnamed: UA2.15, UB2.7, UC1.12, UC2.7
unnamed: UA3.9, UB3.10
unnamed: UA3.15, UB3.15, UF3.9, UL3.11
unnamed: UA4.15, UB4.7, UC4.7, UC5.10
unnamed: UA5.2, UA6.6, UB5.2, UC3.2, UD3.2, UF3.3
unnamed: UA5.15, UB5.7, UM5.1
unnamed: UA6.13, UD6.10, UD6.11
unnamed: UB1.15, UM1.1, UM2.5, UN1.12
unnamed: UB2.15, UC2.10
unnamed: UB3.7, UK3.1
unnamed: UB4.15, UC4.10
unnamed: UB5.15, UM4.5, UM5.2, UN5.12
unnamed: UC1.1, UD2.9
unnamed: UC1.3, UH2.6
unnamed: UC1.5, UD1.4, UD1.10, UD2.1, UD2.13, UE1.4, UE1.13, UE2.1, UE2.13, UJ3.12
unnamed: UC1.8, UC6.2, UK3.2
unnamed: UC1.13, UC2.15, UF3.10
unnamed: UC3.9, UD3.10
unnamed: UC3.15, UC6.3, UD3.15, UF3.5
unnamed: UC5.2, UD4.1, UD4.13, UD5.4, UD5.10, UE4.1, UE4.13, UE5.4, UE5.13, UH3.10
unnamed: UC5.5, UD4.9
unnamed: UC5.6, UH4.6
unnamed: UC5.11, UK3.10
unnamed: UC6.4, UH3.1
unnamed: UC6.12, UF4.11
unnamed: UC6.13, UF5.9, UH5.9, UJ5.9
unnamed: UD1.5, UF1.3
unnamed: UD1.9, UF1.4
unnamed: UD1.3, UD1.11, UD2.3, UD2.11, UE1.3, UE1.11, UE2.3, UE2.11, UM2.12
unnamed: UD2.5, UF2.12
unnamed: UD3.9, UK3.9
unnamed: UD4.5, UF4.5
unnamed: UD4.3, UD4.11, UD5.3, UD5.11, UE4.3, UE4.11, UE5.3, UE5.11, UM4.12
unnamed: UD5.5, UF5.3
unnamed: UD5.9, UF5.4
unnamed: UD6.4, UE6.11
unnamed: UD6.5, UH6.3
unnamed: UD6.13, UJ6.1, UJ6.12, UJ6.13
unnamed: UE1.5, UF1.5
unnamed: UE1.9, UF1.6
unnamed: UE2.5, UF2.5
unnamed: UE2.9, UF2.9
unnamed: UE4.5, UF4.2
unnamed: UE4.9, UF4.9
unnamed: UE5.5, UF5.5
unnamed: UE5.9, UF5.6
unnamed: UE6.3, UN6.3
unnamed: UE6.13, UN6.10
unnamed: UF1.9, UH1.9, UJ1.9, UK1.13
unnamed: UF1.15, UF2.2, UH1.7, UJ1.7
unnamed: UF2.1, UJ1.15, UJ3.11
unnamed: UF2.3, UK1.12
unnamed: UF2.6, UH2.4
unnamed: UF2.8, UH2.5
unnamed: UF2.11, UH2.3
unnamed: UF4.3, UH4.3
unnamed: UF4.6, UH4.4
unnamed: UF4.8, UH4.5
unnamed: UF4.12, UH3.13, UJ5.15
unnamed: UF4.13, UF5.15, UH5.7, UJ5.7
unnamed: UH1.15, UJ1.10
unnamed: UH2.9, UJ2.9, UM3.6
unnamed: UH2.15, UJ2.7, UM1.13, UN3.3
unnamed: UH3.2, UM3.2, UN3.10
unnamed: UH3.4, UH6.2
unnamed: UH3.8, UL4.4
unnamed: UH3.12, UK5.12
unnamed: UH4.9, UJ4.9, UM3.3
unnamed: UH4.15, UJ4.7, UM5.9, UN3.11
unnamed: UH5.15, UJ5.10
unnamed: UJ2.15, UL1.12, UM1.12, UM2.9
unnamed: UJ3.1, UL3.1
unnamed: UJ3.2, UM3.4, UN3.4
unnamed: UJ3.6, UL2.2
unnamed: UJ3.10, UL3.5
unnamed: UJ4.15, UL5.9, UM4.11, UM5.10
unnamed: UJ6.2, UJ6.9
unnamed: UK1.1, UK1.6
unnamed: UK1.2, UK2.2, UK2.6
unnamed: UK1.3, UK2.1, UK2.8
unnamed: UK1.4, UL2.13
unnamed: UK1.5, UK2.11
unnamed: UK3.3, UK3.5, UL3.12
unnamed: UK3.6, UL2.12
unnamed: UK3.11, UL4.12
unnamed: UK3.13, UK4.6
unnamed: UK4.3, UK4.4, UK5.6
unnamed: UK4.5, UK4.8, UK5.5
unnamed: UK5.1, UL4.2
unnamed: UK5.4, UK5.9
unnamed: UK5.10, UL4.10
unnamed: UK5.8, UK5.11, UM4.8
unnamed: UK5.13, UL4.1, UL4.13
unnamed: UL1.3, UL1.9, UM1.10, UM2.10
unnamed: UL1.5, UM1.9, UM2.11
unnamed: UL1.10, UL1.13, UN3.6
unnamed: UL2.1, UL2.9, UL3.4
unnamed: UL2.4, UL3.10
unnamed: UL2.5, UM3.8
unnamed: UL2.6, UN4.5
unnamed: UL2.8, UN4.9
unnamed: UL3.6, UM2.8
unnamed: UL4.5, UM3.11
unnamed: UL4.6, UN4.11
unnamed: UL4.8, UN4.13
unnamed: UL5.3, UM4.9, UM5.13
unnamed: UL5.10, UL5.13, UN3.8
unnamed: UL5.5, UL5.12, UM4.10, UM5.12
unnamed: UM1.2, UM2.4, UN1.3, UN1.9
unnamed: UM1.4, UM2.3, UN1.6
unnamed: UM1.8, UM3.5
unnamed: UM3.1, UM5.8
unnamed: UM4.3, UM5.5, UN5.3, UN5.9
unnamed: UM4.4, UM5.4, UN5.6
unnamed: UN4.2, UN4.3, UN6.8
unnamed: UN6.2, UN6.4
ROM_D0: UA3.11, UB3.11, UC3.11, UD2.2, UD3.11, UE4.2
ROM_D1: UA3.12, UB3.12, UC3.12, UD3.12, UD4.2, UE2.2
ROM_D2: UA3.13, UB3.13, UC3.13, UD3.13, UE2.12, UE4.12
ROM_D3: UA3.14, UB3.14, UC3.14, UD2.12, UD3.14, UD4.12
ROM_D4: UA3.3, UB3.3, UC3.3, UD1.2, UD3.3, UD5.2
ROM_D5: UA3.4, UB3.4, UC3.4, UD1.12, UD3.4, UD5.12
ROM_D6: UA3.5, UB3.5, UC3.5, UD3.5, UE1.2, UE5.2
ROM_D7: UA3.6, UB3.6, UC3.6, UD3.6, UE1.12, UE5.12
S2H1: UH2.13, UK2.13
S2H2: UH4.13, UK4.12
S2V1: UF1.13, UK2.12
S2V2: UF5.13, UK4.13
S4H1: UH2.12, UK2.10, UM3.9
S4H2: UH4.12, UK4.10, UM3.12
S4V1: UF1.12, UK2.5, UL3.9
S4V2: UF5.12, UK4.1, UK5.3
S8H1: UH2.11, UK2.9, UL3.8
S8H2: UH4.11, UK4.9, UK5.2
S8V1: UF1.11, UK2.4, UM3.10
S8V2: UF5.11, UK4.2, UM3.13
SRS1: UK1.10, UK1.11
SRS2: UC6.10, UC6.11
START: UD6.1, UE6.8, UH3.3
THR1Q: UA1.9, UB1.9, UM1.6
THR2Q: UA5.9, UB5.9, UM5.6
THW1Q: UF3.12, UL3.3, UM2.6
THW2Q: UC6.5, UF3.2, UM4.6
TVR1Q: UA2.9, UB2.9, UC1.11, UC2.9, UK1.8
TVR2Q: UA4.9, UB4.9, UC4.9, UC5.8, UC6.9
TVW2: UC4.15, UC5.9, UF3.4
V128: UE6.9, UJ6.3, UJ6.11
VRST1Q: UA2.1, UB2.1, UC2.1
VRST2Q: UA4.1, UB4.1, UC4.1
